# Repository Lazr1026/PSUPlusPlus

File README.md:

# wiiu-psu
The wiiu-psu (or PSU++) is a regulator board for the Wii U, minus the core rails (1v/1.15v).
It is based off the PSU-Plus, so all rails have a limit of 3A (this only really matters for 5v).

### Features
- All low-current regulators required for the Wii U to function.
- Bonus 3v3 rail (STBY) for the RTC to power on the system.
- 1.25v regulator for WUP-01 motherboards (or if you wanted to remove the stock one).
    - 1.25v can be enabled/disabled with a simple jumper.

The intent is to be used for the Wii U Mini, but if you find another use for this board, have at it!  
There are two VIN pads. The smaller one is used to power the STBY regulator, while the bigger one is to power all of the other regulators.

### Credits
[CrazyGadget](https://github.com/CrazyGadgetMods) / [YveltalGriffin](https://github.com/mackieks): The original PSU-Plus regulator board.  
[BitBuilt](https://bitbuilt.net/): Being pretty fucking cool.

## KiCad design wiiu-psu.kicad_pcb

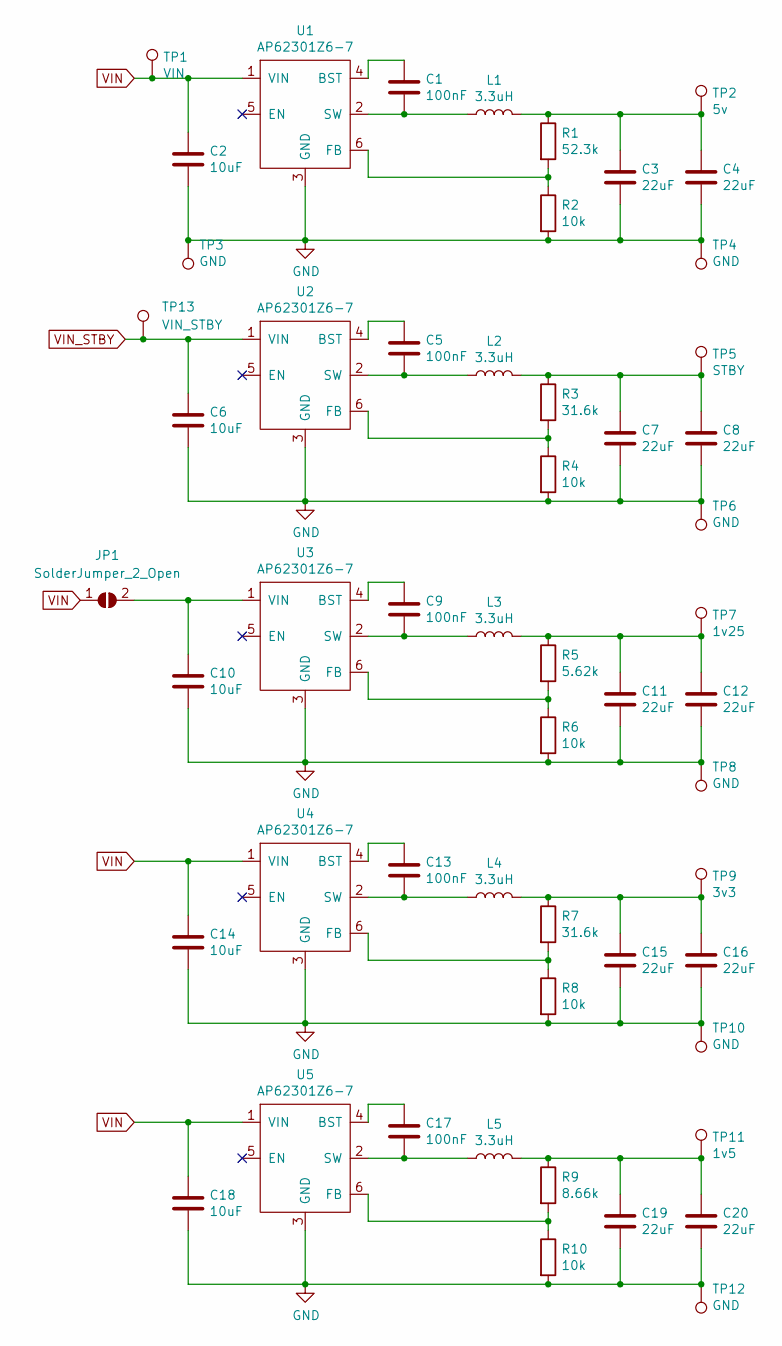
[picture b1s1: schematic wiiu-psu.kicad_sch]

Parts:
C1, C5, C9, C13, C17: 100nF; C_0402_1005Metric
C2, C6, C10, C14, C18: 10uF; C_0805_2012Metric
C3, C4, C7, C8, C11, C12, C15, C16, C19, C20: 22uF; C_0603_1608Metric
JP1: SolderJumper_2_Open; SolderJumper-2_P1.3mm_Open_Pad1.0x1.5mm
L1, L2, L3, L4, L5: 3.3uH; 1919
R1: 52.3k; R_0402_1005Metric
R2, R4, R6, R8, R10: 10k; R_0402_1005Metric
R3, R7: 31.6k; R_0402_1005Metric
R5: 5.62k; R_0402_1005Metric
R9: 8.66k; R_0402_1005Metric
TP1: VIN; TestPoint_Pad_2.0x2.0mm
TP2: 5v; TestPoint_Pad_2.0x2.0mm
TP3, TP4, TP6, TP8, TP10, TP12: GND; TestPoint_Pad_2.0x2.0mm
TP5: STBY; TestPoint_Pad_2.0x2.0mm
TP7: 1v25; TestPoint_Pad_2.0x2.0mm
TP9: 3v3; TestPoint_Pad_2.0x2.0mm
TP11: 1v5; TestPoint_Pad_2.0x2.0mm
TP13: VIN_STBY; TestPoint_Pad_1.0x1.0mm
U1, U2, U3, U4, U5: AP62301Z6-7; SOT-563mod

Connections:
GND: C2.1, C3.2, C4.2, C6.1, C7.2, C8.2, C10.1, C11.2, C12.2, C14.1, C15.2, C16.2, C18.1, C19.2, C20.2, R2.2, R4.2, R6.2, R8.2, R10.2, TP3.1, TP4.1, TP6.1, TP8.1, TP10.1, TP12.1, U1.3 (GND), U2.3 (GND), U3.3 (GND), U4.3 (GND), U5.3 (GND)
unnamed: C3.1, C4.1, L1.2, R1.1, TP2.1
unnamed: C7.1, C8.1, L2.2, R3.1, TP5.1
unnamed: C11.1, C12.1, L3.2, R5.1, TP7.1
unnamed: C15.1, C16.1, L4.2, R7.1, TP9.1
unnamed: C19.1, C20.1, L5.2, R9.1, TP11.1
unnamed: C10.2, JP1.2 (B), U3.1 (VIN)
unnamed: C1.1, U1.4 (BST)
unnamed: R1.2, R2.1, U1.6 (FB)
unnamed: C1.2, L1.1, U1.2 (SW)
unnamed: C5.1, U2.4 (BST)
unnamed: R3.2, R4.1, U2.6 (FB)
unnamed: C5.2, L2.1, U2.2 (SW)
unnamed: C9.1, U3.4 (BST)
unnamed: R5.2, R6.1, U3.6 (FB)
unnamed: C9.2, L3.1, U3.2 (SW)
unnamed: C13.1, U4.4 (BST)
unnamed: R7.2, R8.1, U4.6 (FB)
unnamed: C13.2, L4.1, U4.2 (SW)
unnamed: C17.1, U5.4 (BST)
unnamed: R9.2, R10.1, U5.6 (FB)
unnamed: C17.2, L5.1, U5.2 (SW)
VIN: C2.2, C14.2, C18.2, JP1.1 (A), TP1.1, U1.1 (VIN), U4.1 (VIN), U5.1 (VIN)
VIN_STBY: C6.2, TP13.1, U2.1 (VIN)

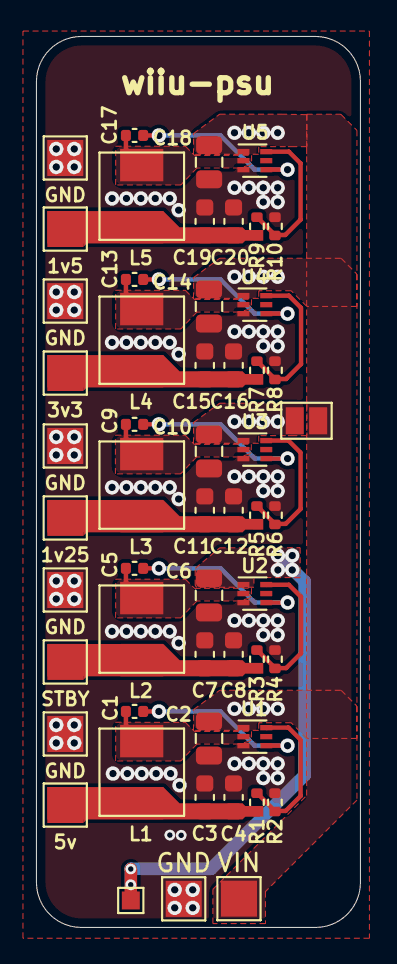
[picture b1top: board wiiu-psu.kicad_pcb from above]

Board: 2 copper layers, 18.0 x 49.5 mm, 54 parts (0 on the bottom side), 24 nets.

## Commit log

2024-10-14 Fix image link
2024-10-14 Fix formatting
2024-10-14 slap a license on here
